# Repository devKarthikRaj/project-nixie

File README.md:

# Project Nixie

<br> This is a Nixie Clock created by two engineering students. </br>
## Overview
Nixie Tubes were used back in the day to display numbers and text, until the world was taken over by LEDs. </br>

### Featuring our contraption...
This project aims to bring back a relic of the past, but packed with modern tech. This clock comes with features like Wi-Fi, BLE, onboard sensors, ARGB lighting etc., all of which is controlled through a mobile app.<br />

<br />
___

## Design

Our Nixie clock is designed from the ground up with individual drivers for every digit (no multiplexing), Wi-Fi/BLE, built-in timekeeping, and ruggedized power supply. The custom firmware drivers allow for full dimming and/or crossfading control of the digits. Users can also customize the firmware to suit their needs. <br>

The clock is housed in a 3D printed dark grey nylon enclosure, providing a high quality feel and look. <br>

## Features
- Wi-Fi/BLE for NTP sync/smart home functionality
- Dual core microcontroller (ESP32) for complex tasks
- High accuracy RTC with TCXO to accurately keep track of time once sync'ed
- High efficiency, rugged power components to ensure long service life
- Individually addressible RGB tube illumination
- Individually driven digits which make crossfading or other such effects light on I/O as compared to multiplexed
- Replaceable tubes (trim leads to approx 8-10mm)<br />
<br><br />

## Android App Control
Our Nixie Tube clock can be controlled through our Android app - NixieCon. NixieCon connects to the hardware via Bluetooth. Download the app [here](https://github.com/devKarthikRaj/project-nixie/blob/master/App/app/release/app-release.apk).<br>

<div align="center">

</div>

## Links
[Hardware Documentation](https://github.com/devKarthikRaj/project-nixie/blob/master/Nixie%20Clock/Nixie%20Tube%20Clock%20User%20Guide.pdf) <br>
[Nixie Tube HAL](https://github.com/edward62740/NixieDisplay-HAL) <br>

___ 
## License and Usage
This project and the resources contained therein may be used in accordance with the [LICENSE](https://github.com/devKarthikRaj/project-nixie/blob/master/LICENSE).

### Disclaimer (and read the license)

The reproduction and/or use of this project, and any resulting consequences thereof are completely at your own risk. The high-voltage supply contained in this design is capable of outputting up to 260 volts unadjusted, which can cause severe injury or death. There may be spurious emissions or other forms of EMI which may disrupt the usage of other appliances, from which a malfunction may cause severe injury or death. During normal operation, the power components radiate a non-trivial amount of heat, which may result in a fire hazard if poorly ventilated. IN-14 nixie tubes (used here) contain small amounts of mercury, which may be released if the tube is broken. Read the license.
___ 

## Developers
[Karthik Raj](https://github.com/devKarthikRaj) <br>
[Edward](https://github.com/edward62740)

Released under the AGPL-3.0 License

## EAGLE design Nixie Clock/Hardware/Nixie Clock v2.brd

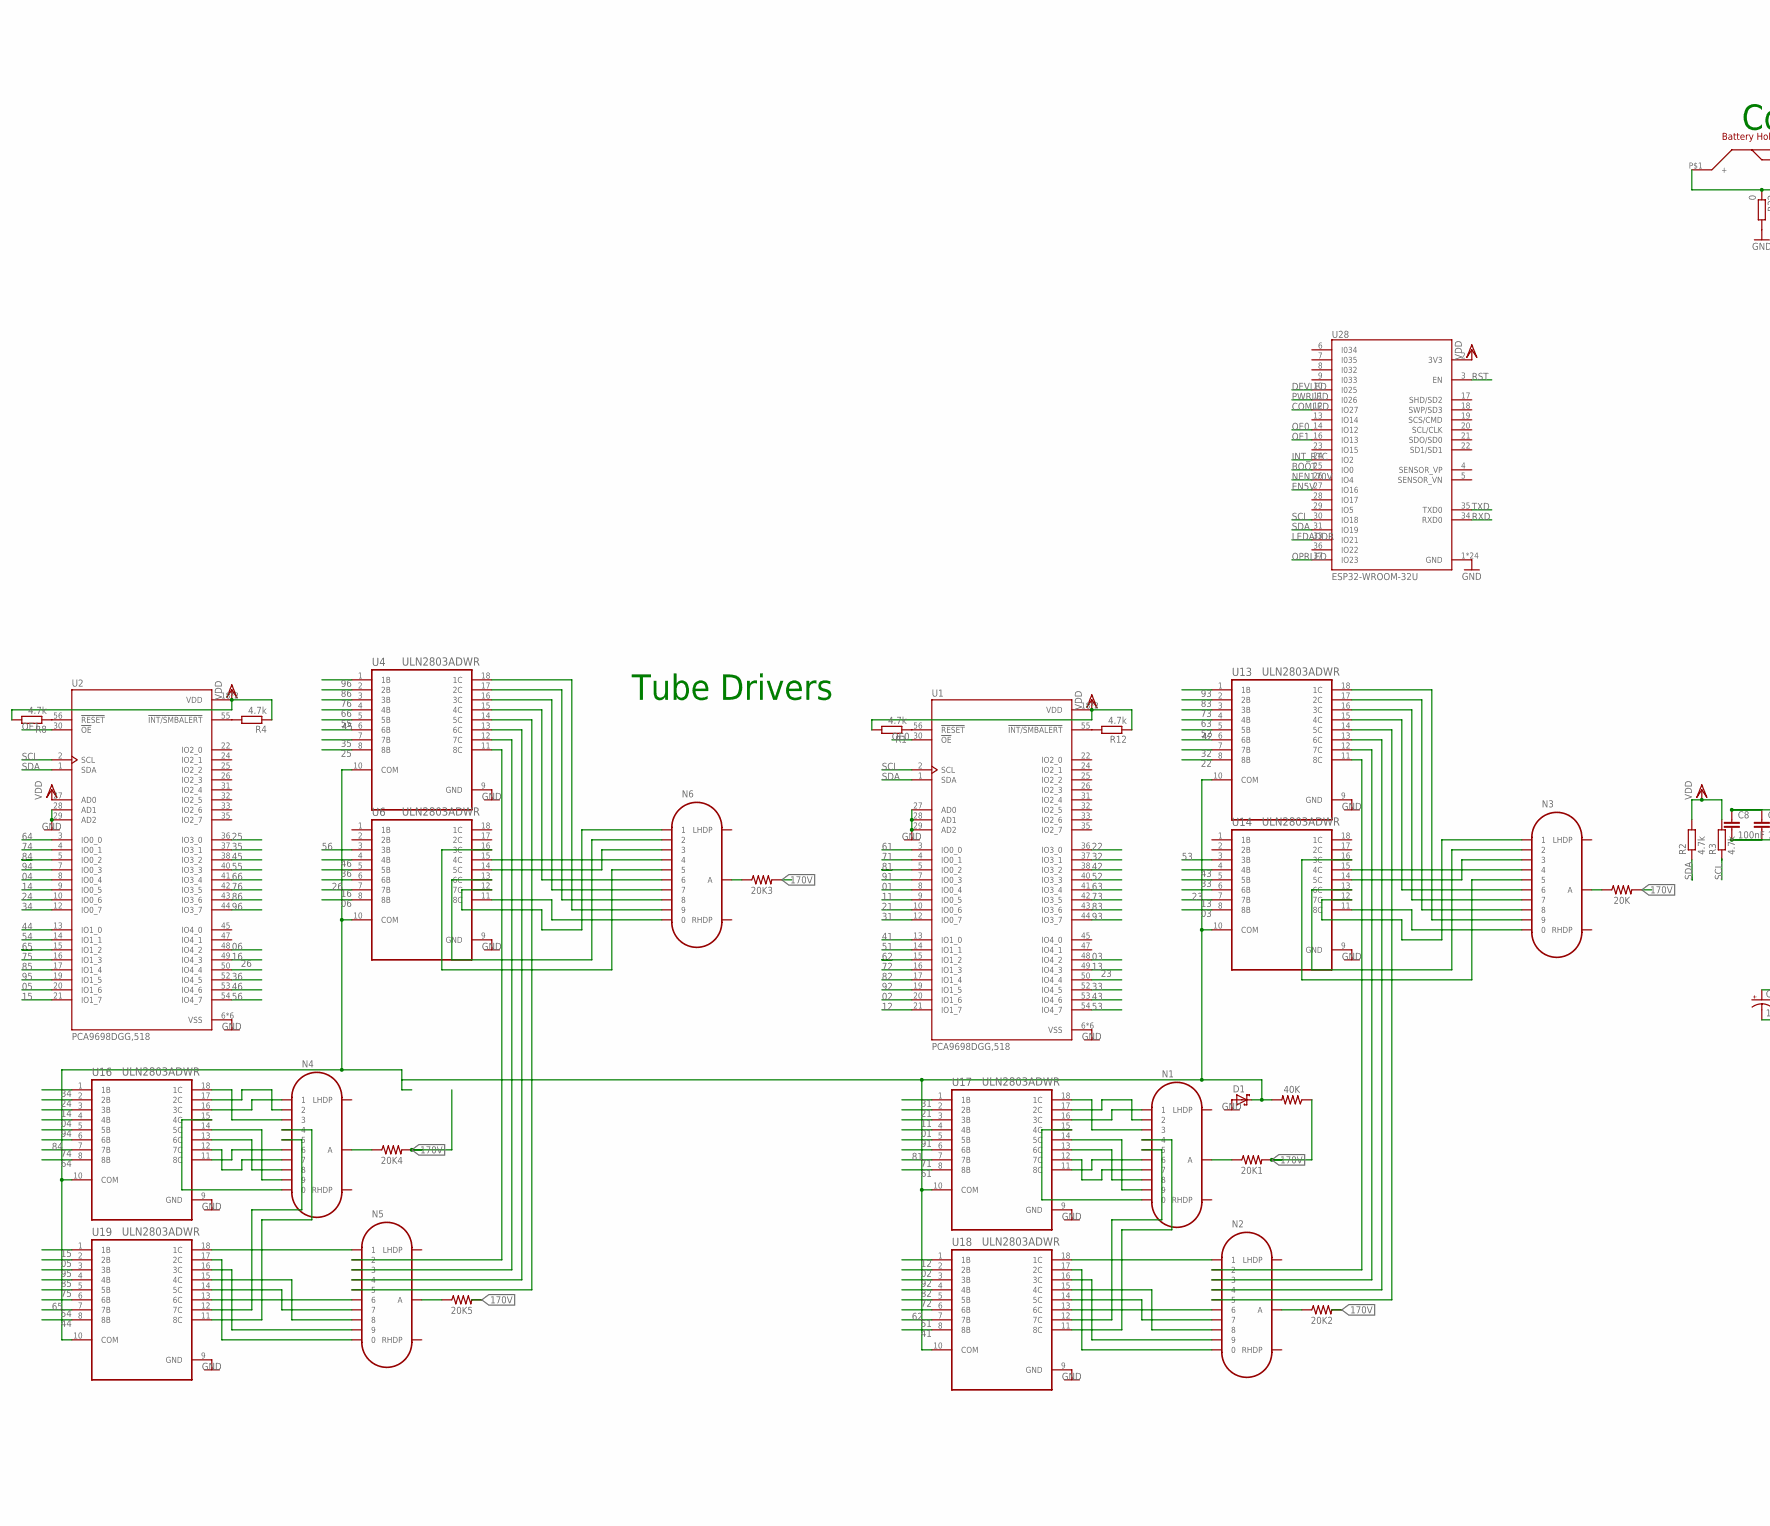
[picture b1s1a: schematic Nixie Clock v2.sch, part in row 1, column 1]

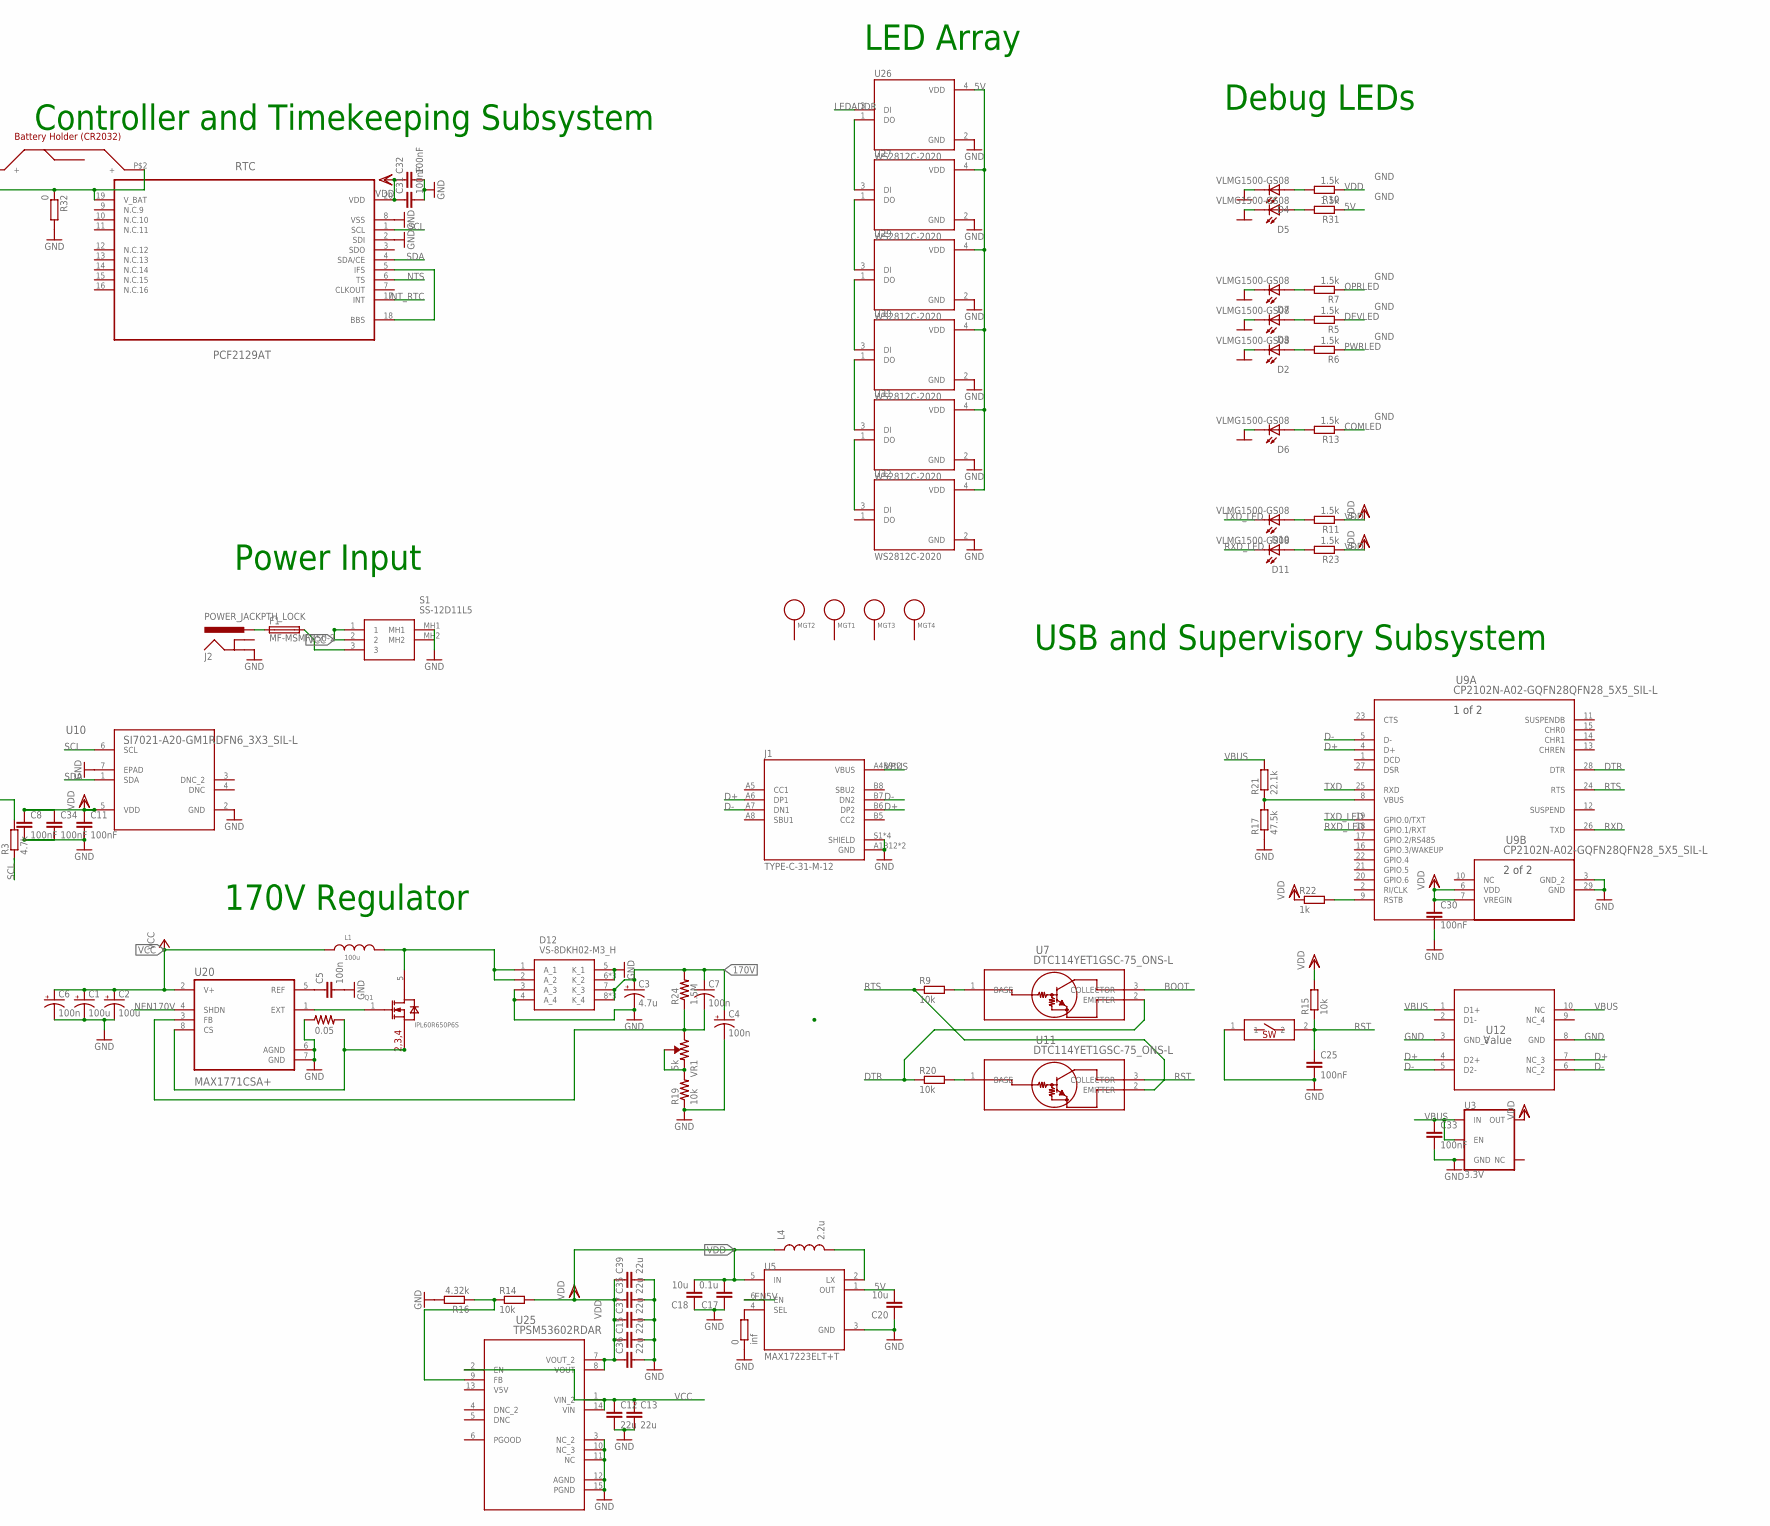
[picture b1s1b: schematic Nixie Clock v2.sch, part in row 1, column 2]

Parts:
0: inf; R0402
0.05, 20K, 20K1, 20K2, 20K3, 20K4, 20K5, 40K: 0.05; 1210
C1, C2: 100u; E3,5-8
C3: 4.7u; E3,5-8
C4, C6: 100n; A/3216-18W
C5: 100n; C0402
C7: 100n; C1206K
C8, C11, C25, C30, C31, C32, C33, C34: 100nF; C0402
C12, C13, C15, C35, C36, C37, C39: 22u; C0603R
C17: 0.1u; C0402
C18, C20: 10u; C0402
D1: SCHOTTKY-DIODE; DIODE_SMB
D2, D3, D4, D5, D6, D7, D10, D11: VLMG1500-GS08; LEDC1005X35N
D12: VS-8DKH02-M3_H; VS8DKH02M3H
F1: MF-MSMF050-2; 1812
J1: TYPE-C-31-M-12; HRO_TYPE-C-31-M-12
J2: POWER_JACKPTH_LOCK; POWER_JACK_PTH_LOCK
L1: 100u; WE-PD_1260/1245/1280/1210
L4: 2.2u; L0603
MGT1, MGT2, MGT3, MGT4: BEAGLEBONEBLACK_MOUNTING_HOLE
N1, N2, N3, N4, N5, N6: IN-14
Q1: IPL60R650P6S; INF-PG-TSON-8-2
R1, R2, R3, R4, R8, R12: 4.7k; R0402
R5, R6, R7, R10, R11, R13, R23, R31: 1.5k; R0402
R9, R14, R15, R20: 10k; R0402
R16: 4.32k; R0402
R17: 47.5k; R0402
R19: 10k; M1206
R21: 22.1k; R0402
R22: 1k; R0402
R24: 1.5M; M1206
R32: 0; R0402
RESET: SMDSWITCH; RESC4217X170
S1: SS-12D11L5; SS12D11L5
U1, U2: PCA9698DGG,518; SOP50P810X120-56N
U3: 3.3V; SOT23-5
U4, U6, U13, U14, U16, U17, U18, U19: ULN2803ADWR; SOIC127P1030X265-18N
U5: MAX17223ELT+T; PSON65P200X200X80-6N
U7, U11: DTC114YET1GSC-75_ONS-L; SC-75_ONS-L
U9: CP2102N-A02-GQFN28QFN28_5X5_SIL-L; QFN28_5X5_SIL-L
U10: SI7021-A20-GM1RDFN6_3X3_SIL-L; DFN6_3X3_SIL-L
U12: Value; DQA0010A
U20: MAX1771CSA+; SOIC127P600X175-8N
U25: TPSM53602RDAR; B3QFN15_RDA_TEX
U26, U27, U29, U30, U31, U32: WS2812C-2020; LED_WS2812C-2020
U28: ESP32-WROOM-32U; XCVR_ESP32-WROOM-32U
U$1: PCF2129AT
U$2: HOLDER
VR1: 5k; TRIMPOT-SMD-3MM-CLOSED

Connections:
01: U1.8 (IO0_4), U17.4 (4B)
02: U1.20 (IO1_6), U18.2 (2B)
03: U1.48 (IO4_2), U14.8 (8B)
04: U2.8 (IO0_4), U16.4 (4B)
05: U2.20 (IO1_6), U19.2 (2B)
5V: C20.2, R31.1, U5.1 (OUT), U26.4 (VDD), U27.4 (VDD), U29.4 (VDD), U30.4 (VDD), U31.4 (VDD), U32.4 (VDD)
06: U2.48 (IO4_2), U6.8 (8B)
11: U1.9 (IO0_5), U17.3 (3B)
12: U1.21 (IO1_7), U18.1 (1B)
13: U1.49 (IO4_3), U14.7 (7B)
14: U2.9 (IO0_5), U16.3 (3B)
15: U2.21 (IO1_7), U19.1 (1B)
16: U2.49 (IO4_3), U6.7 (7B)
21: U1.10 (IO0_6), U17.2 (2B)
22: U1.36 (IO3_0), U13.8 (8B)
23: U1.50 (IO4_4), U14.6 (6B)
24: U2.10 (IO0_6), U16.2 (2B)
25: U2.36 (IO3_0), U4.8 (8B)
26: U2.50 (IO4_4), U6.6 (6B)
31: U1.12 (IO0_7), U17.1 (1B)
32: U1.37 (IO3_1), U13.7 (7B)
33: U1.52 (IO4_5), U14.5 (5B)
34: U2.12 (IO0_7), U16.1 (1B)
35: U2.37 (IO3_1), U4.7 (7B)
36: U2.52 (IO4_5), U6.5 (5B)
41: U1.13 (IO1_0), U18.8 (8B)
42: U1.38 (IO3_2), U13.6 (6B)
43: U1.53 (IO4_6), U14.4 (4B)
44: U2.13 (IO1_0), U19.8 (8B)
45: U2.38 (IO3_2), U4.6 (6B)
46: U2.53 (IO4_6), U6.4 (4B)
51: U1.14 (IO1_1), U18.7 (7B)
52: U1.40 (IO3_3), U13.5 (5B)
53: U1.54 (IO4_7), U14.3 (3B)
54: U2.14 (IO1_1), U19.7 (7B)
55: U2.40 (IO3_3), U4.5 (5B)
56: U2.54 (IO4_7), U6.3 (3B)
61: U1.3 (IO0_0), U17.8 (8B)
62: U1.15 (IO1_2), U18.6 (6B)
63: U1.41 (IO3_4), U13.4 (4B)
64: U2.3 (IO0_0), U16.8 (8B)
65: U2.15 (IO1_2), U19.6 (6B)
66: U2.41 (IO3_4), U4.4 (4B)
71: U1.4 (IO0_1), U17.7 (7B)
72: U1.16 (IO1_3), U18.5 (5B)
73: U1.42 (IO3_5), U13.3 (3B)
74: U2.4 (IO0_1), U16.7 (7B)
75: U2.16 (IO1_3), U19.5 (5B)
76: U2.42 (IO3_5), U4.3 (3B)
81: U1.5 (IO0_2), U17.6 (6B)
82: U1.17 (IO1_4), U18.4 (4B)
83: U1.43 (IO3_6), U13.2 (2B)
84: U2.5 (IO0_2), U16.6 (6B)
85: U2.17 (IO1_4), U19.4 (4B)
86: U2.43 (IO3_6), U4.2 (2B)
91: U1.7 (IO0_3), U17.5 (5B)
92: U1.19 (IO1_5), U18.3 (3B)
93: U1.44 (IO3_7), U13.1 (1B)
94: U2.7 (IO0_3), U16.5 (5B)
95: U2.19 (IO1_5), U19.3 (3B)
96: U2.44 (IO3_7), U4.1 (1B)
170V: 20K.2, 20K1.2, 20K2.2, 20K3.2, 20K4.2, 20K5.2, 40K.1, C3.+, C4.+, C7.1, D12.7 (K_3), D12.8 (K_4), D12.9 (K_4), D12.12 (K_4), R24.2
BOOT: U7.3 (COLLECTOR), U28.25 (IO0)
COMLED: R13.1, U28.12 (IO27)
D+: J1.A6 (DP1), J1.B6 (DP2), U9.4 (D+), U12.4 (D2+), U12.7 (NC_3)
D-: J1.A7 (DN1), J1.B7 (DN2), U9.5 (D-), U12.5 (D2-), U12.6 (NC_2)
DEVLED: R5.1, U28.10 (I025)
DTR: R20.1, U7.2 (EMITTER), U9.28 (DTR)
EN5V: U5.6 (EN), U28.27 (IO16)
GND: 0.1, 0.05.1, C1.-, C2.-, C3.-, C4.-, C5.2, C6.-, C8.2, C11.2, C12.2, C13.2, C15.2, C17.1, C18.1, C20.1, C25.2, C30.2, C31.2, C32.2, C33.2, C34.2, C35.2, C36.2, C37.2, C39.2, D1.A (C), D2.2, D3.2, D4.2, D5.2, D6.2, D7.2, D12.3 (A_3), D12.4 (A_4), D12.5 (K_1), D12.6 (K_2), D12.10 (K_2), D12.11 (K_2), J1.A1B12 (GND), J1.B1A12 (GND), J1.S1 (SHIELD), J1.S2 (SHIELD), J1.S3 (SHIELD), J1.S4 (SHIELD), J2.GND, R16.2, R17.1, R19.1, R32.2, RESET.1, S1.MH1, S1.MH2, U1.6 (VSS), U1.11 (VSS), U1.23 (VSS), U1.27 (AD0), U1.28 (AD1), U1.29 (AD2), U1.34 (VSS), U1.39 (VSS), U1.51 (VSS), U2.6 (VSS), U2.11 (VSS), U2.23 (VSS), U2.28 (AD1), U2.29 (AD2), U2.34 (VSS), U2.39 (VSS), U2.51 (VSS), U3.2 (GND), U4.9 (GND), U5.3 (GND), U6.9 (GND), U9.3 (GND_2), U9.29 (GND), U10.2 (GND), U10.7 (EPAD), U12.3 (GND_2), U12.8 (GND), U13.9 (GND), U14.9 (GND), U16.9 (GND), U17.9 (GND), U18.9 (GND), U19.9 (GND), U20.6 (AGND), U20.7 (GND), U25.3 (NC_2), U25.10 (NC_3), U25.11 (NC), U25.12 (AGND), U25.15 (PGND), U26.2 (GND), U27.2 (GND), U28.1 (GND), U28.15 (GND), U28.38 (GND), U28.G.1 (GND), U28.G.2 (GND), U28.G.4 (GND), U28.G.5 (GND), U28.G.6 (GND), U28.G.7 (GND), U28.G.8 (GND), U28.G.9 (GND), U28.G.10 (GND), U28.G.11 (GND), U28.G.12 (GND), U28.G.13 (GND), U28.G.14 (GND), U28.G.15 (GND), U28.G.16 (GND), U28.G.17 (GND), U28.G.18 (GND), U28.G.19 (GND), U28.G.20 (GND), U28.G.21 (GND), U28.G.22 (GND), U29.2 (GND), U30.2 (GND), U31.2 (GND), U32.2 (GND), U$1.2 (SDI), U$1.8 (VSS)
INT_RTC: U28.24 (IO2), U$1.17 (INT)
LEDADDR: U26.3 (DI), U28.33 (IO21)
unnamed: F1.1, J2.PWR
unnamed: C5.1, U20.5 (REF)
unnamed: 20K1.1, N1.A
unnamed: Q1.1 (GATE), U20.1 (EXT)
unnamed: 0.05.2, Q1.2 (SOURCE), Q1.3 (SOURCE), Q1.4 (SOURCE), U20.8 (CS)
unnamed: D12.1 (A_1), D12.2 (A_2), L1.2, Q1.5 (DRAIN)
unnamed: N2.0, U18.17 (2C)
unnamed: N2.9, U18.16 (3C)
unnamed: 20K2.1, N2.A
unnamed: R19.2, VR1.1 (CCW), VR1.2 (WIPER)
unnamed: C7.2, R24.1, U20.3 (FB), VR1.3 (CW)
unnamed: N2.8, U18.15 (4C)
unnamed: N2.7, U18.14 (5C)
unnamed: N1.5, U18.12 (7C)
unnamed: 20K.1, N3.A
unnamed: N2.6, U18.13 (6C)
unnamed: 0.2, U5.4 (SEL)
unnamed: D3.1, R5.2
unnamed: D7.1, R7.2
unnamed: L4.2, U5.2 (LX)
unnamed: 20K4.1, N4.A
unnamed: N2.1, U18.18 (1C)
unnamed: R17.2, R21.1, U9.8 (VBUS)
unnamed: D2.1, R6.2
unnamed: D4.1, R10.2
unnamed: D5.1, R31.2
unnamed: D6.1, R13.2
unnamed: N2.2, U13.11 (8C)
unnamed: R20.2, U11.1 (BASE)
unnamed: R9.2, U7.1 (BASE)
unnamed: N1.6, U17.11 (8C)
unnamed: N1.7, U17.12 (7C)
unnamed: R22.2, U9.9 (RSTB)
unnamed: D10.1, R11.2
unnamed: D11.1, R23.2
unnamed: F1.2, S1.3
unnamed: N1.8, U17.13 (6C)
unnamed: N1.9, U17.14 (5C)
unnamed: N1.0, U17.15 (4C)
unnamed: N1.1, U17.16 (3C)
unnamed: N1.2, U17.17 (2C)
unnamed: N1.3, U17.18 (1C)
unnamed: N2.3, U13.12 (7C)
unnamed: N1.4, U18.11 (8C)
unnamed: N2.4, U13.13 (6C)
unnamed: N2.5, U13.14 (5C)
unnamed: N3.6, U13.15 (4C)
unnamed: N3.7, U13.16 (3C)
unnamed: N3.8, U13.17 (2C)
unnamed: N3.9, U13.18 (1C)
unnamed: N3.0, U14.11 (8C)
unnamed: N3.1, U14.12 (7C)
unnamed: N3.2, U14.13 (6C)
unnamed: N3.3, U14.14 (5C)
unnamed: N3.4, U14.15 (4C)
unnamed: N3.5, U14.16 (3C)
unnamed: R4.2, U2.55 (!INT/SMBALERT)
unnamed: N4.6, U16.11 (8C)
unnamed: N4.7, U16.12 (7C)
unnamed: N4.8, U16.13 (6C)
unnamed: N4.9, U16.14 (5C)
unnamed: N4.0, U16.15 (4C)
unnamed: N4.1, U16.16 (3C)
unnamed: N4.2, U16.17 (2C)
unnamed: 40K.2, D1.C (A), U4.10 (COM), U6.10 (COM), U13.10 (COM), U14.10 (COM), U16.10 (COM), U17.10 (COM), U18.10 (COM), U19.10 (COM)
unnamed: N4.3, U16.18 (1C)
unnamed: N4.4, U19.11 (8C)
unnamed: N4.5, U19.12 (7C)
unnamed: N5.0, U19.17 (2C)
unnamed: N5.9, U19.16 (3C)
unnamed: N5.8, U19.15 (4C)
unnamed: N5.7, U19.14 (5C)
unnamed: N5.6, U19.13 (6C)
unnamed: N5.1, U19.18 (1C)
unnamed: N5.2, U4.11 (8C)
unnamed: N5.3, U4.12 (7C)
unnamed: N5.4, U4.13 (6C)
unnamed: N5.5, U4.14 (5C)
unnamed: N6.6, U4.15 (4C)
unnamed: N6.7, U4.16 (3C)
unnamed: N6.8, U4.17 (2C)
unnamed: N6.9, U4.18 (1C)
unnamed: N6.0, U6.11 (8C)
unnamed: N6.1, U6.12 (7C)
unnamed: N6.2, U6.13 (6C)
unnamed: N6.3, U6.14 (5C)
unnamed: N6.4, U6.15 (4C)
unnamed: N6.5, U6.16 (3C)
unnamed: R14.1, R16.1, U25.9 (FB)
unnamed: 20K5.1, N5.A
unnamed: 20K3.1, N6.A
unnamed: R1.1, U1.56 (!RESET)
unnamed: R12.2, U1.55 (!INT/SMBALERT)
unnamed: R32.1, U$1.19 (V_BAT), U$2.P$1, U$2.P$2
unnamed: R8.1, U2.56 (!RESET)
unnamed: U26.1 (DO), U27.3 (DI)
unnamed: U27.1 (DO), U29.3 (DI)
unnamed: U29.1 (DO), U30.3 (DI)
unnamed: U30.1 (DO), U31.3 (DI)
unnamed: U31.1 (DO), U32.3 (DI)
unnamed: U$1.5 (IFS), U$1.18 (BBS)
NEN170V: U20.4 (SHDN), U28.26 (IO4)
NTS: U$1.6 (TS)
OE0: U1.30 (!OE), U28.14 (IO12)
OE1: U2.30 (!OE), U28.16 (IO13)
OPRLED: R7.1, U28.37 (IO23)
PWRLED: R6.1, U28.11 (I026)
RST: C25.1, R15.1, RESET.2, U11.3 (COLLECTOR), U28.3 (EN)
RTS: R9.1, U9.24 (RTS), U11.2 (EMITTER)
RXD: U9.26 (TXD), U28.34 (RXD0)
RXD_LED: D11.2, U9.18 (GPIO.1/RXT)
SCL: R3.1, U1.2 (SCL), U2.2 (SCL), U10.6 (SCL), U28.30 (IO18), U$1.1 (SCL)
SDA: R2.1, U1.1 (SDA), U2.1 (SDA), U10.1 (SDA), U28.31 (IO19), U$1.4 (SDA/CE)
TXD: U9.25 (RXD), U28.35 (TXD0)
TXD_LED: D10.2, U9.19 (GPIO.0/TXT)
VBUS: C33.1, J1.A4B9 (VBUS), J1.B4A9 (VBUS), R21.2, U3.1 (IN), U3.3 (EN), U12.1 (D1+), U12.10 (NC)
VCC: C1.+, C2.+, C6.+, C12.1, C13.1, L1.1, S1.1, S1.2, U20.2 (V+), U25.1 (VIN_2), U25.2 (EN), U25.14 (VIN)
VDD: C8.1, C11.1, C15.1, C17.2, C18.2, C30.1, C31.1, C32.1, C34.1, C35.1, C36.1, C37.1, C39.1, L4.1, R1.2, R2.2, R3.2, R4.1, R8.2, R10.1, R11.1, R12.1, R14.2, R15.2, R22.1, R23.1, U1.18 (VDD), U1.46 (VDD), U2.18 (VDD), U2.27 (AD0), U2.46 (VDD), U3.5 (OUT), U5.5 (IN), U9.6 (VDD), U9.7 (VREGIN), U10.5 (VDD), U25.7 (VOUT_2), U25.8 (VOUT), U28.2 (3V3), U$1.20 (VDD)

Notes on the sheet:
Tube Drivers
Controller and Timekeeping Subsystem
LED Array
Debug LEDs
Power Input
170V Regulator
USB and Supervisory Subsystem

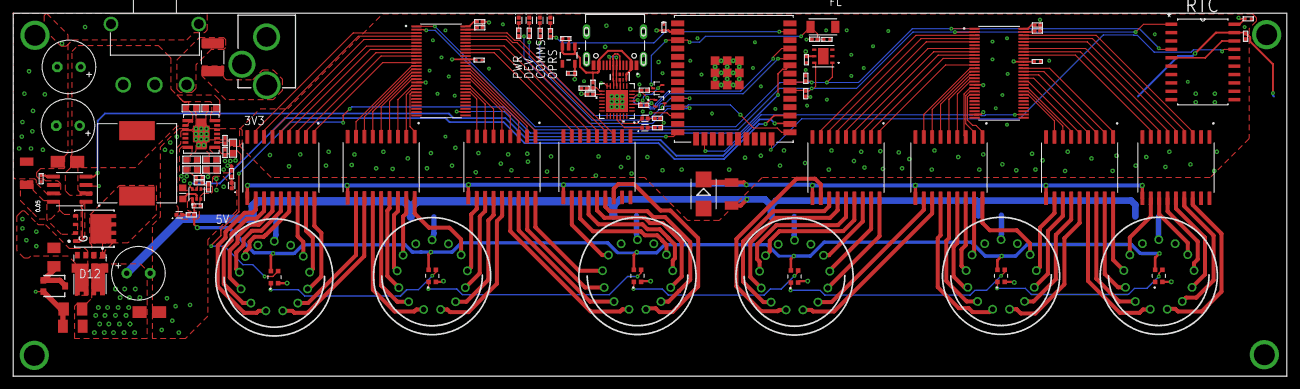
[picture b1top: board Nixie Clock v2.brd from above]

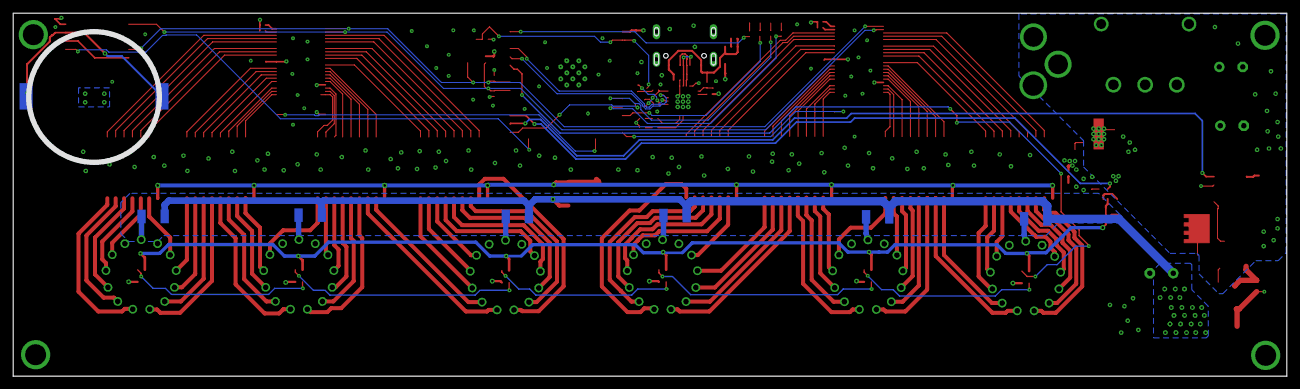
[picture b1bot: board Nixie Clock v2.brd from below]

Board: 4 copper layers, 193.0 x 55.0 mm, 116 parts (7 on the bottom side), 189 nets.

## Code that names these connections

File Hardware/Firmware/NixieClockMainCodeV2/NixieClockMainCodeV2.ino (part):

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/* Pin definitions */
#define rtcInt          2 //RTC Interrupt 
#define en170V          4 //170V enable - Pull to low to enable               
#define en5V           16 //5V enable - Pull to high to enable
#define supervisor5V   17 //5V rail blackout indicator - If low, 5V blackout!!!
#define twimIntSCL     18 //I2C SCK 
#define twimIntSDA     19 //I2C SDA
#define ledBus         21 //WS2812 RGBLED Control Bus
#define sysLed         22 //System LED - UNUSED FOR NOW 
#define opsLed         23 //Operation LED - Blinking if RTC interrupt is triggered and Nixie Tubes are updated
#define devLed         25 //Dev LED - UNUSED FOR NOW
#define pwrLed         26 //Power LED for power system (5V & 170V) status
#define comLed         27 //Fast Blinking if not connected to app... Slow Blinking if connected to app


/* Nixie tube pinouts */
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  //IO Definitions
  pinMode(rtcInt, INPUT_PULLUP); //***Interrupt pin has to be set as input pullup***
  pinMode(en170V, OUTPUT);
  pinMode(en5V, OUTPUT);
  pinMode(supervisor5V, INPUT);
  pinMode(ledBus, OUTPUT);
  pinMode(sysLed, OUTPUT);
  pinMode(opsLed, OUTPUT);
  pinMode(devLed, OUTPUT);
  pinMode(pwrLed, OUTPUT);
  pinMode(comLed, OUTPUT);

  //Turn on the 5V and 170V supplies (3.3V is auto turned on cuz ESP32 runs off it)
  digitalWrite(en5V, HIGH);
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
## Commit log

2021-09-02 Initial commit of project nixie hardware-software combined repo
2021-09-02 cleared all folders for cleaning
2021-09-02 cleared repo for hardware-software repo combine op
2021-09-02 added readme
2021-09-02 added hardware documentation pdf
2021-09-19 Create LICENSE
2021-10-01 changed android app icon
2021-10-07 Fixed android 11 bt issue and completed num2disp library implementation
2021-11-17 Removed bt verification and bug fixes
2021-11-17 Updated readme and apks
2021-12-30 Fixed readme img loading issues
2022-01-09 Attempt to fix readme image load problem
2022-01-09 Attempt to fix readme img load problem
2022-01-20 test
2022-01-20 Added updated PCB files
2022-01-20 Added clock.jpeg
2022-01-26 Added pictures
2022-01-26 Resized pictures and deleted unused pictures
2022-01-26 Edited readme
2022-01-26 Edited readme and resized pictures
2022-03-03 Bug Fixes
2022-03-03 Updated to use new Nixie driver library
2022-03-04 Increased execution speed
2022-03-04 Generated APK
2022-03-04 Feature update
2022-03-05 v2 Update
2022-03-08 Added media and updated readme
2022-03-08 Added mea and updated readme
2022-03-08 Removed lib
2022-03-08 Added media
2022-03-16 Restructured folders
2022-03-16 Changed I2C clock speed
2022-05-10 fixed dependencies
2022-05-31 Updated dependencies
2022-07-14 Added ifdb example
2022-09-01 Added pages
2022-09-01 Create CNAME
2022-09-01 Update CNAME

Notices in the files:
parts and their libraries:
SparkFun-Resistors: Licensing: Creative Commons ShareAlike 4.0 International - https://creativecommons.org/licenses/by-sa/4.0
Wurth_Elektronik_Passive_rev18f: Copyright: Würth Elektronik
COPYRIGHT: Copyright (C) 2018 Accelerated Designs. All rights reserved
